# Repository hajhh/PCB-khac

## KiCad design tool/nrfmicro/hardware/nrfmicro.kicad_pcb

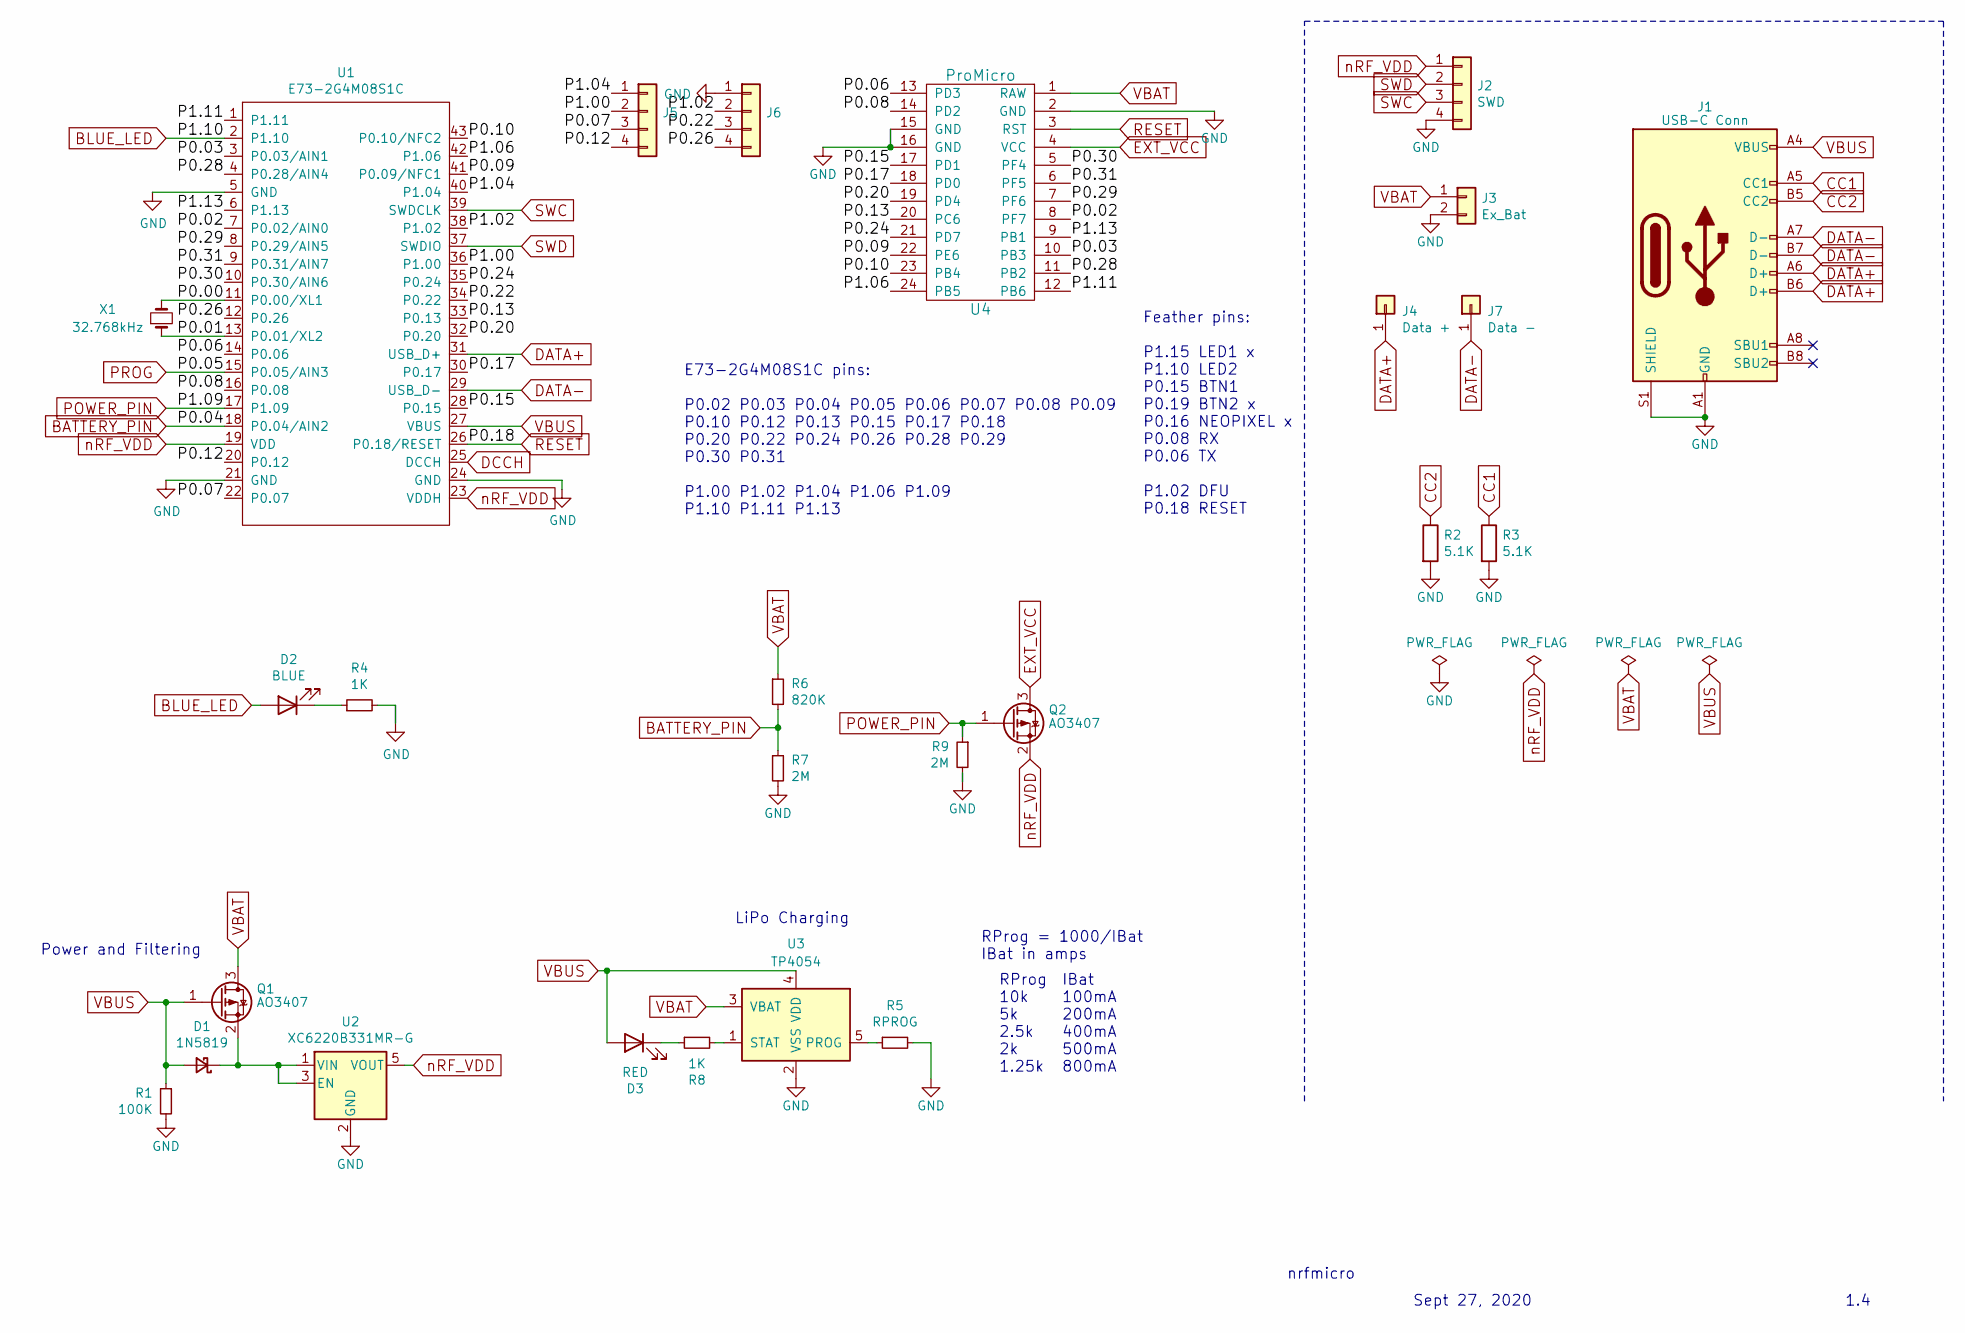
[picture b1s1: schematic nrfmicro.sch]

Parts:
D1: 1N5819; D_SOD-323F
D2: BLUE; LED_0603_1608Metric
D3: RED; LED_0603_1608Metric
J1: USB-C Conn; usb-c
J2: SWD; connector_swd
J3: Ex_Bat; connector_bat
J4: Data +; PinSocket_1x01_P2.54mm_Vertical
J5, J6: conn_01x04
J7: Data -; PinSocket_1x01_P2.54mm_Vertical
Q1, Q2: AO3407; SOT-23
R1: 100K; R_0603_1608Metric
R2, R3: 5.1K; R_0603_1608Metric
R4, R8: 1K; R_0603_1608Metric
R5: RPROG; R_0603_1608Metric
R6: 820K; R_0603_1608Metric
R7, R9: 2M; R_0603_1608Metric
U1: E73-2G4M08S1C; E73-2G4M08S1C-52840
U2: XC6220B331MR-G; SOT-23-5
U3: TP4054; SOT-23-5
U4: ProMicro; pro_micro
X1: 32.768kHz; Crystal_SMD_MicroCrystal_CM9V-T1A-2Pin_1.6x1.0mm

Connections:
/P0.00: U1.11 (P0.00/XL1), X1.2
/P0.01: U1.13 (P0.01/XL2), X1.1
/P0.02: U1.7 (P0.02/AIN0), U4.8 (PF7)
/P0.03: U1.3 (P0.03/AIN1), U4.10 (PB3)
/P0.06: U1.14 (P0.06), U4.13 (PD3)
/P0.07: J5.3, U1.22 (P0.07)
/P0.08: U1.16 (P0.08), U4.14 (PD2)
/P0.09: U1.41 (P0.09/NFC1), U4.22 (PE6)
/P0.10: U1.43 (P0.10/NFC2), U4.23 (PB4)
/P0.12: J5.4, U1.20 (P0.12)
/P0.13: U1.33 (P0.13), U4.20 (PC6)
/P0.15: U1.28 (P0.15), U4.17 (PD1)
/P0.17: U1.30 (P0.17), U4.18 (PD0)
/P0.20: U1.32 (P0.20), U4.19 (PD4)
/P0.22: J6.3, U1.34 (P0.22)
/P0.24: U1.35 (P0.24), U4.21 (PD7)
/P0.26: J6.4, U1.12 (P0.26)
/P0.28: U1.4 (P0.28/AIN4), U4.11 (PB2)
/P0.29: U1.8 (P0.29/AIN5), U4.7 (PF6)
/P0.30: U1.10 (P0.30/AIN6), U4.5 (PF4)
/P0.31: U1.9 (P0.31/AIN7), U4.6 (PF5)
/P1.00: J5.2, U1.36 (P1.00)
/P1.02: J6.2, U1.38 (P1.02)
/P1.04: J5.1, U1.40 (P1.04)
/P1.06: U1.42 (P1.06), U4.24 (PB5)
/P1.11: U1.1 (P1.11), U4.12 (PB6)
/P1.13: U1.6 (P1.13), U4.9 (PB1)
BATTERY_PIN: R6.2, R7.1, U1.18 (P0.04/AIN2)
BLUE_LED: D2.2 (A), U1.2 (P1.10)
CC1: J1.A5 (CC1), R3.1
CC2: J1.B5 (CC2), R2.1
DATA+: J1.A6 (D+), J1.B6 (D+), J4.1, U1.31 (USB_D+)
DATA-: J1.A7 (D-), J1.B7 (D-), J7.1, U1.29 (USB_D-)
DCCH: U1.25 (DCCH)
EXT_VCC: Q2.3 (D), U4.4 (VCC)
GND: J1.A1 (GND), J1.A12 (GND), J1.B1 (GND), J1.B12 (GND), J1.S1 (SHIELD), J2.4, J3.2, J6.1, R1.2, R2.2, R3.2, R4.2, R5.2, R7.2, R9.2, U1.5 (GND), U1.21 (GND), U1.24 (GND), U2.2 (GND), U3.2 (VSS), U4.2 (GND), U4.15 (GND), U4.16 (GND)
unnamed: D1.1 (K), Q1.2 (S), U2.1 (VIN), U2.3 (EN)
unnamed: D2.1 (K), R4.1
unnamed: D3.1 (K), R8.1
unnamed: R5.1, U3.5 (PROG)
unnamed: R8.2, U3.1 (STAT)
POWER_PIN: Q2.1 (G), R9.1, U1.17 (P1.09)
PROG: U1.15 (P0.05/AIN3)
RESET: U1.26 (P0.18/RESET), U4.3 (RST)
SWC: J2.3, U1.39 (SWDCLK)
SWD: J2.2, U1.37 (SWDIO)
VBAT: J3.1, Q1.3 (D), R6.1, U3.3 (VBAT), U4.1 (RAW)
VBUS: D1.2 (A), D3.2 (A), J1.A4 (VBUS), J1.A9 (VBUS), J1.B4 (VBUS), J1.B9 (VBUS), Q1.1 (G), R1.1, U1.27 (VBUS), U3.4 (VDD)
nRF_VDD: J2.1, Q2.2 (S), U1.19 (VDD), U1.23 (VDDH), U2.5 (VOUT)

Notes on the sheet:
nrfmicro
Sept 27, 2020
1.4
E73-2G4M08S1C pins: P0.02 P0.03 P0.04 P0.05 P0.06 P0.07 P0.08 P0.09 P0.10 P0.12 P0.13 P0.15 P0.17 P0.18 P0.20 P0.22 P0.24 P0.26 P0.28 P0.29 P0.30 P0.31 P1.00 P1.02 P1.04 P1.06 P1.09 P1.10 P1.11 P1.13
Feather pins: P1.15 LED1 x P1.10 LED2 P0.15 BTN1 P0.19 BTN2 x P0.16 NEOPIXEL x P0.08 RX P0.06 TX P1.02 DFU P0.18 RESET
Power and Filtering
LiPo Charging
RProg 10k 5k 2.5k 2k 1.25k
IBat 100mA 200mA 400mA 500mA 800mA
RProg = 1000/IBat IBat in amps

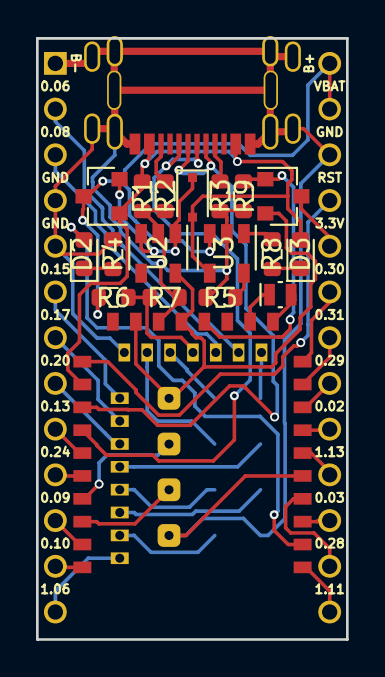
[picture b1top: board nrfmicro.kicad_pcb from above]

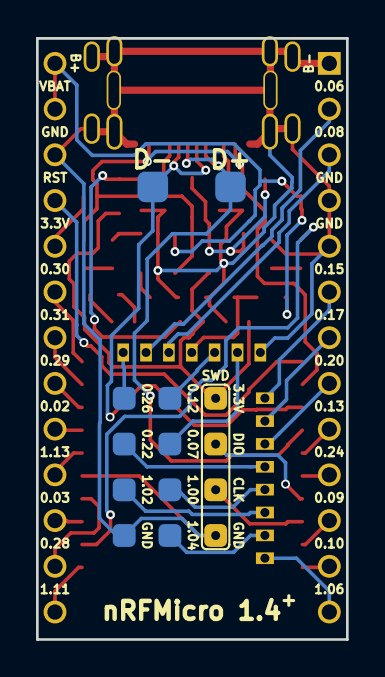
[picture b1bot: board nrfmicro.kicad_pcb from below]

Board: 2 copper layers, 17.2 x 33.4 mm, 26 parts (5 on the bottom side), 47 nets.
